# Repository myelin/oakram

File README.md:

# A3010 RAM board

Originally by Tim Tashpulatov (tnt23), later updated by Daniel Jameson (drdpj).

This branch is based on Daniel's last 2-layer version, and contains tweaks by Phillip Pearson (myelin).

[Stardot thread](https://stardot.org.uk/forums/viewtopic.php?f=16&t=11214)

Pictures
--------

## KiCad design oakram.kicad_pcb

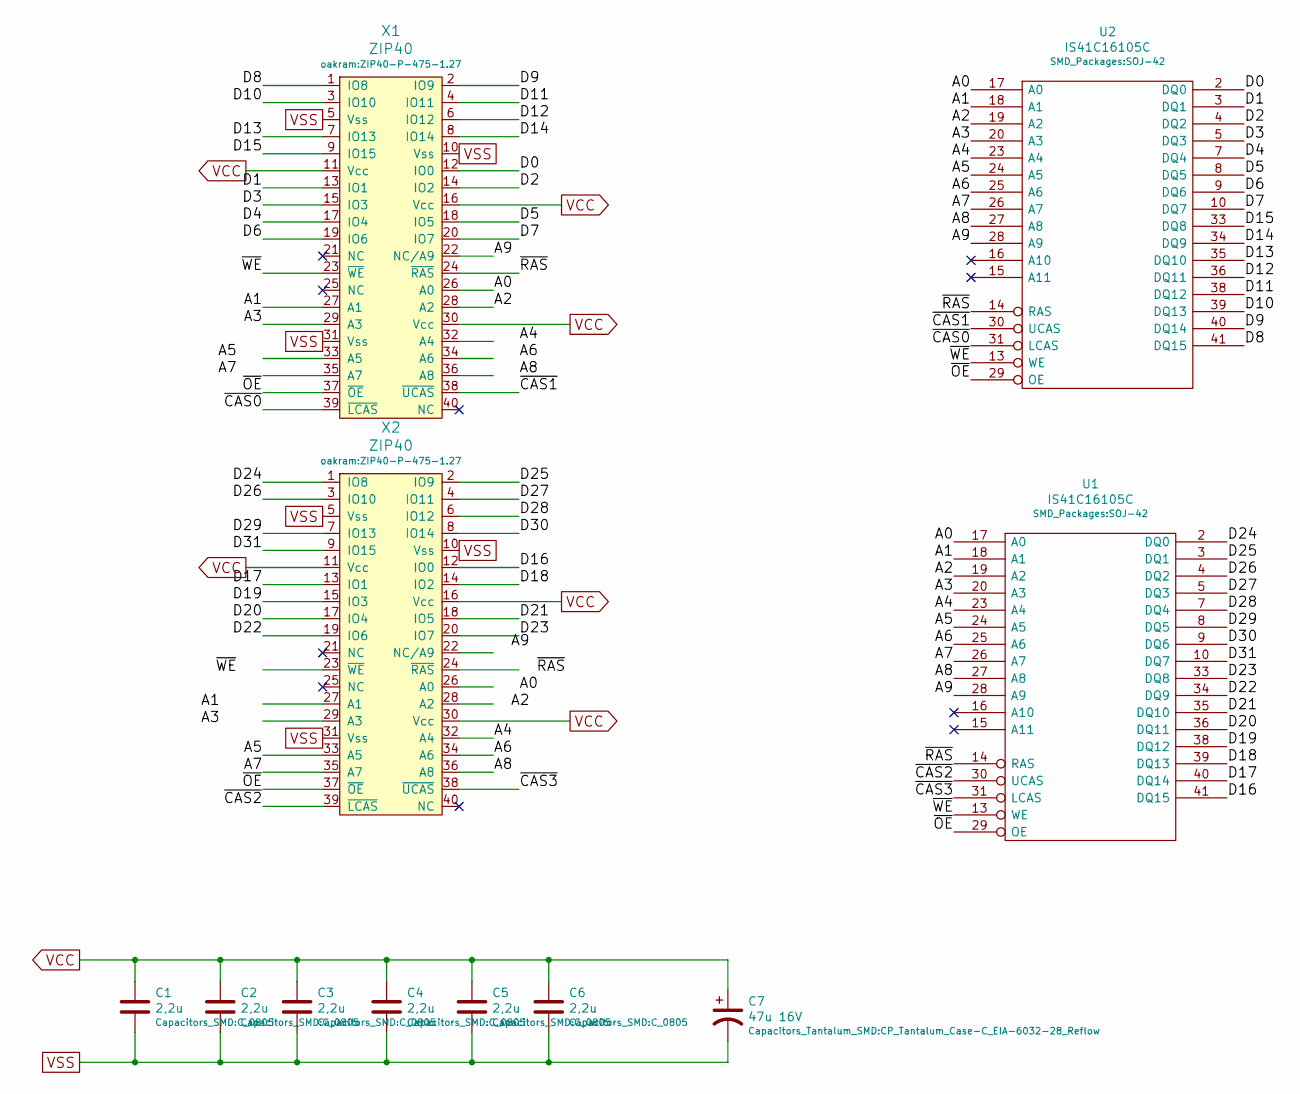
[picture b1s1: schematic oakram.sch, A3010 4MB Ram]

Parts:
C1, C2, C3, C4, C5, C6: 2,2u; C_0805
C7: 47u 16V; CP_Tantalum_Case-C_EIA-6032-28_Reflow
U1, U2: IS41C16105C; SOJ-42
X1, X2: ZIP40; ZIP40-P-475-1.27

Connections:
/A0: U1.17 (A0), U2.17 (A0), X1.26 (A0)
/A1: U1.18 (A1), U2.18 (A1), X1.27 (A1)
/A2: U1.19 (A2), U2.19 (A2), X1.28 (A2)
/A3: U1.20 (A3), U2.20 (A3), X1.29 (A3)
/A4: U1.23 (A4), U2.23 (A4), X2.32 (A4)
/A5: U1.24 (A5), U2.24 (A5), X2.33 (A5)
/A6: U1.25 (A6), U2.25 (A6), X2.34 (A6)
/A7: U1.26 (A7), U2.26 (A7), X2.35 (A7)
/A8: U1.27 (A8), U2.27 (A8), X2.36 (A8)
/A9: U1.28 (A9), U2.28 (A9), X1.22 (NC/A9)
/D0: U2.2 (DQ0), X1.12 (IO0)
/D1: U2.3 (DQ1), X1.13 (IO1)
/D2: U2.4 (DQ2), X1.14 (IO2)
/D3: U2.5 (DQ3), X1.15 (IO3)
/D4: U2.7 (DQ4), X1.17 (IO4)
/D5: U2.8 (DQ5), X1.18 (IO5)
/D6: U2.9 (DQ6), X1.19 (IO6)
/D7: U2.10 (DQ7), X1.20 (IO7)
/D8: U2.41 (DQ15), X1.1 (IO8)
/D9: U2.40 (DQ14), X1.2 (IO9)
/D10: U2.39 (DQ13), X1.3 (IO10)
/D11: U2.38 (DQ12), X1.4 (IO11)
/D12: U2.36 (DQ11), X1.6 (IO12)
/D13: U2.35 (DQ10), X1.7 (IO13)
/D14: U2.34 (DQ9), X1.8 (IO14)
/D15: U2.33 (DQ8), X1.9 (IO15)
/D16: U1.41 (DQ15), X2.12 (IO0)
/D17: U1.40 (DQ14), X2.13 (IO1)
/D18: U1.39 (DQ13), X2.14 (IO2)
/D19: U1.38 (DQ12), X2.15 (IO3)
/D20: U1.36 (DQ11), X2.17 (IO4)
/D21: U1.35 (DQ10), X2.18 (IO5)
/D22: U1.34 (DQ9), X2.19 (IO6)
/D23: U1.33 (DQ8), X2.20 (IO7)
/D24: U1.2 (DQ0), X2.1 (IO8)
/D25: U1.3 (DQ1), X2.2 (IO9)
/D26: U1.4 (DQ2), X2.3 (IO10)
/D27: U1.5 (DQ3), X2.4 (IO11)
/D28: U1.7 (DQ4), X2.6 (IO12)
/D29: U1.8 (DQ5), X2.7 (IO13)
/D30: U1.9 (DQ6), X2.8 (IO14)
/D31: U1.10 (DQ7), X2.9 (IO15)
/~CAS0: U2.31 (LCAS), X1.39 (~LCAS)
/~CAS1: U2.30 (UCAS), X1.38 (~UCAS)
/~CAS2: U1.30 (UCAS), X2.39 (~LCAS)
/~CAS3: U1.31 (LCAS), X2.38 (~UCAS)
/~RAS: U1.14 (RAS), U2.14 (RAS), X1.24 (~RAS)
/~WE: U1.13 (WE), U2.13 (WE), X1.23 (~WE)
VCC: C1.1, C2.1, C3.1, C4.1, C5.1, C6.1, C7.1, U1.1 (VCC), U1.6 (VCC), U1.21 (VCC), U2.1 (VCC), U2.6 (VCC), U2.21 (VCC), X1.11 (Vcc), X1.16 (Vcc), X1.30 (Vcc), X2.11 (Vcc), X2.16 (Vcc), X2.30 (Vcc)
VSS: C1.2, C2.2, C3.2, C4.2, C5.2, C6.2, C7.2, U1.22 (VSS), U1.37 (VSS), U1.42 (VSS), U2.22 (VSS), U2.37 (VSS), U2.42 (VSS), X1.5 (Vss), X1.10 (Vss), X1.31 (Vss), X2.5 (Vss), X2.10 (Vss), X2.31 (Vss)

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
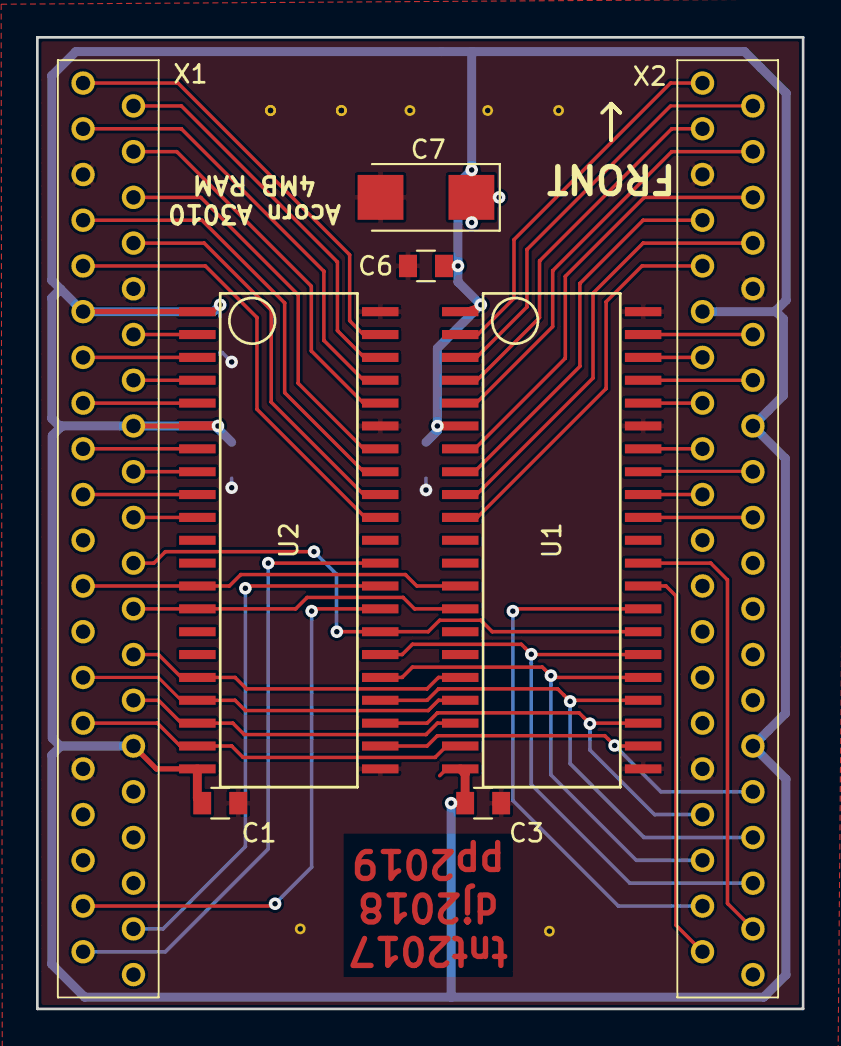
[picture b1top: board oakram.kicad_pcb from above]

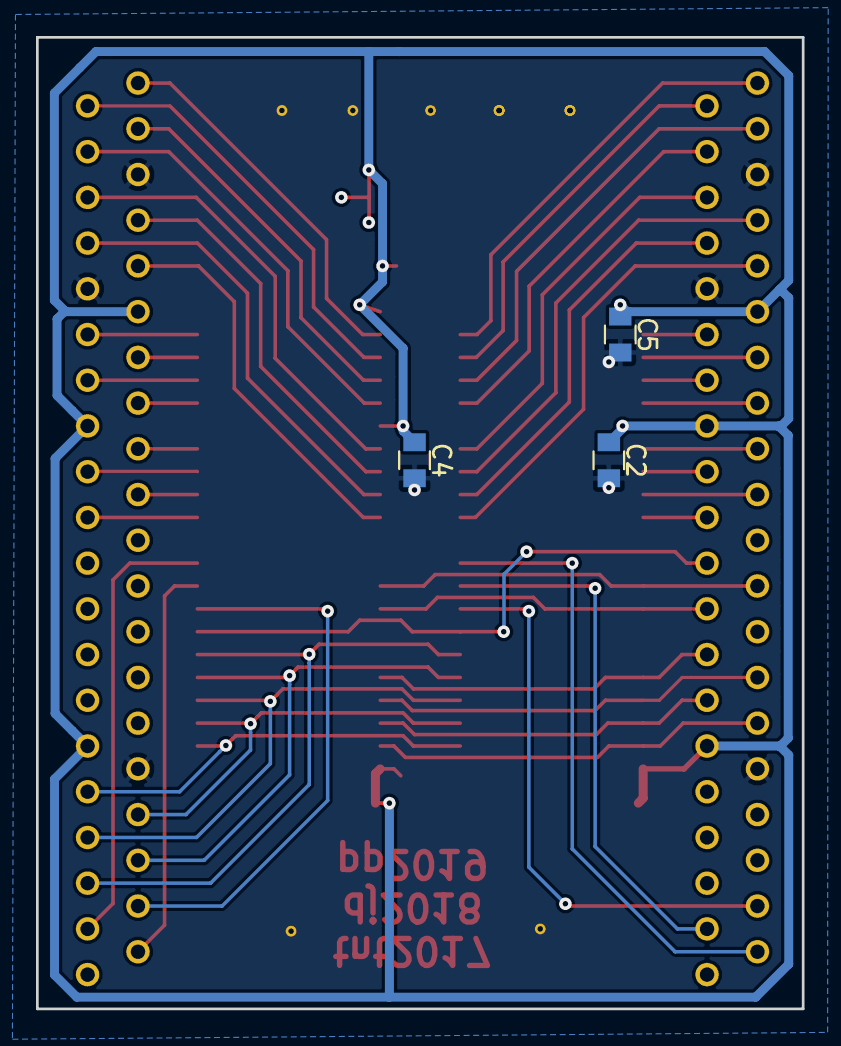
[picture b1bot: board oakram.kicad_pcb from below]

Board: 2 copper layers, 42.5 x 54.0 mm, 11 parts (3 on the bottom side), 52 nets.

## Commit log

2019-05-18 Removed backup files
2019-05-18 Added my Makefile based build system
2019-05-18 Added README.md
2019-05-18 oakramv2.zip from https://stardot.org.uk/forums/viewtopic.php?f=16&t=11214&p=193124#p193117
2019-05-18 Fix image links in README.md
2019-05-18 oakramv2.zip from https://stardot.org.uk/forums/viewtopic.php?f=16&t=11214&p=193124#p193124
2019-05-18 oakramv2.zip from https://stardot.org.uk/forums/viewtopic.php?f=16&t=11214&p=193124#p193131
2019-05-18 oakramv2.zip from https://stardot.org.uk/forums/viewtopic.php?f=16&t=11214&start=270#p193151 -- danielj ordered a set of these from JLC and they worked
2019-05-18 Messing around with grounding etc
2019-05-18 oakramv3 from https://stardot.org.uk/forums/viewtopic.php?f=16&t=11214&p=237523#p201999
2019-05-18 Added 7mil clearance and changed min width on all pours to 7mil, then fixed DRC
2019-05-18 Removed split planes on B.Cu, replaced with one big ground plane and a VCC ring
2019-05-18 Added pp2019 to author list on F.Cu
2019-05-18 Reduced hole and pad size on ZIP sockets, tightened top layer plane clearance to 6 mil, moved data lines to allow ground plane to pour between every pair
